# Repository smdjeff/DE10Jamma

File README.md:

# DE10Jamma

JAMMA/NeoGeo MVS audio, video & control IO for DE10-Nano.

[https://github.com/MisterJamma/DE10Jamma](https://github.com/MisterJamma/DE10Jamma)

Discussion thread: [https://www.atari-forum.com/viewtopic.php?f=120&t=38793](https://www.atari-forum.com/viewtopic.php?f=120&t=38793)

## Description

### Overview
DE10Jamma allows a DE10-Nano board to be connected directly to an arcade cabinet as simply as possible. USB and HDMI serial interfaces are not used, in order to remain as close as possible to the original arcade hardware and avoid unnecessary cost or complexity.

Pull-down resistors on AUDIO_L and AUDIO_R pins allow this board to be detected and coexist with other MiSTer hardware using common rbf files for the cores. See [this commit](https://github.com/MisterJamma/Arcade-GnG_MiSTer/commit/6c7786a7f790a5277f337f6b245e99f6ca4c25ff).

##### Future Developments
Future developments in RTL and software to more fully support DE10Jamma

1. Allow player controls to be used in the OSD.

### Inputs
Inputs are [RC filtered](https://wiki.neogeodev.org/index.php?title=CRE401) to give EMI protection to the FPGA.

No multiplexing, polling or debouncing of the inputs ensures **zero** additional latency & jitter. Cabinet switches are presented to arcade cores exactly as they would be on a real arcade PCB. Arcade cores will include necessary debouncing either in replicated hardware of the original PCB, or in software running on that hardware. When buttons are passed to the ARM host CPU for controlling the UI & selecting arcade cores, the inputs should debounced appropriately in hardware or software.

### Audio Output
2 pole RC filters convert PWM output from DE10-Nano to analog signal. Mono/Stereo jumper JP1 allows stereo signal for MVS wired cabinets, or mono signal for JAMMA wired cabinets. With no jumper fitted, there will be no audio output for the left channel.

2 channel power amplifier drives the speaker loads.

### Video Output
Composite sync is generated by DE10-Nano.

Three 6bit R-2R DACs convert the digital output from DE10-Nano to analog RGB. A single 2R value used in parallel to generate the R value with tighter tolerance. Part-to-part tolerance is typically significantly better than absolute part tolerance, so using a single 2R value for all resistors in the DAC should improve linearity.

No additional latency or incompatibility from HDMI logic and low quality HDMI converters. Resistive DACs are commonly used on arcade PCBs, and allow the original odd resolutions & refresh rates to be supported correctly. Output level is not noticeably lower than a NeoGeo MVS, and well within adjustment range on arcade monitors.

### DC Power Output
DC power output is provided for the DE10-Nano. This should be connected using a short [2.1mm male-male cable](https://www.google.com/search?q=2.1mm+male+to+male&tbm=isch), such as used to connect guitar effects pedals to a power supply.

Arcade power supplies are typically adjustable. DE10-Nano has regulation for lower voltage supplies, and should operate correctly from nominal +5v settings. If +5v rail is adjusted too high, the DE10-Nano's over-voltage protection circuitry will not allow the board to power up.

## Parts List
See BOM in fabrication outputs file

###### Notes
   1. Part numbers from [LSSC](https://lcsc.com/) are provided where possible. Values for some components do not match the schematic, and have been adjusted to reduce the number of different components.

   1. J1, J2 and J6 should be inserted into PCB from above, using DE10-Nano to set correct depth. Solder carefully from above & trim to length. Pins should protrude approximately 0.25" from the PCB

   1. J9 is only required for cabinets with 2.5mm pitch JST kick harness connector. It may also be possible to use 0.1" pitch J11 connector with existing kick harness, as the difference in pitch is minimal for a 10way connector.

   1. A 20mm deep fan running on a lower voltage is recommended for reduced noise.

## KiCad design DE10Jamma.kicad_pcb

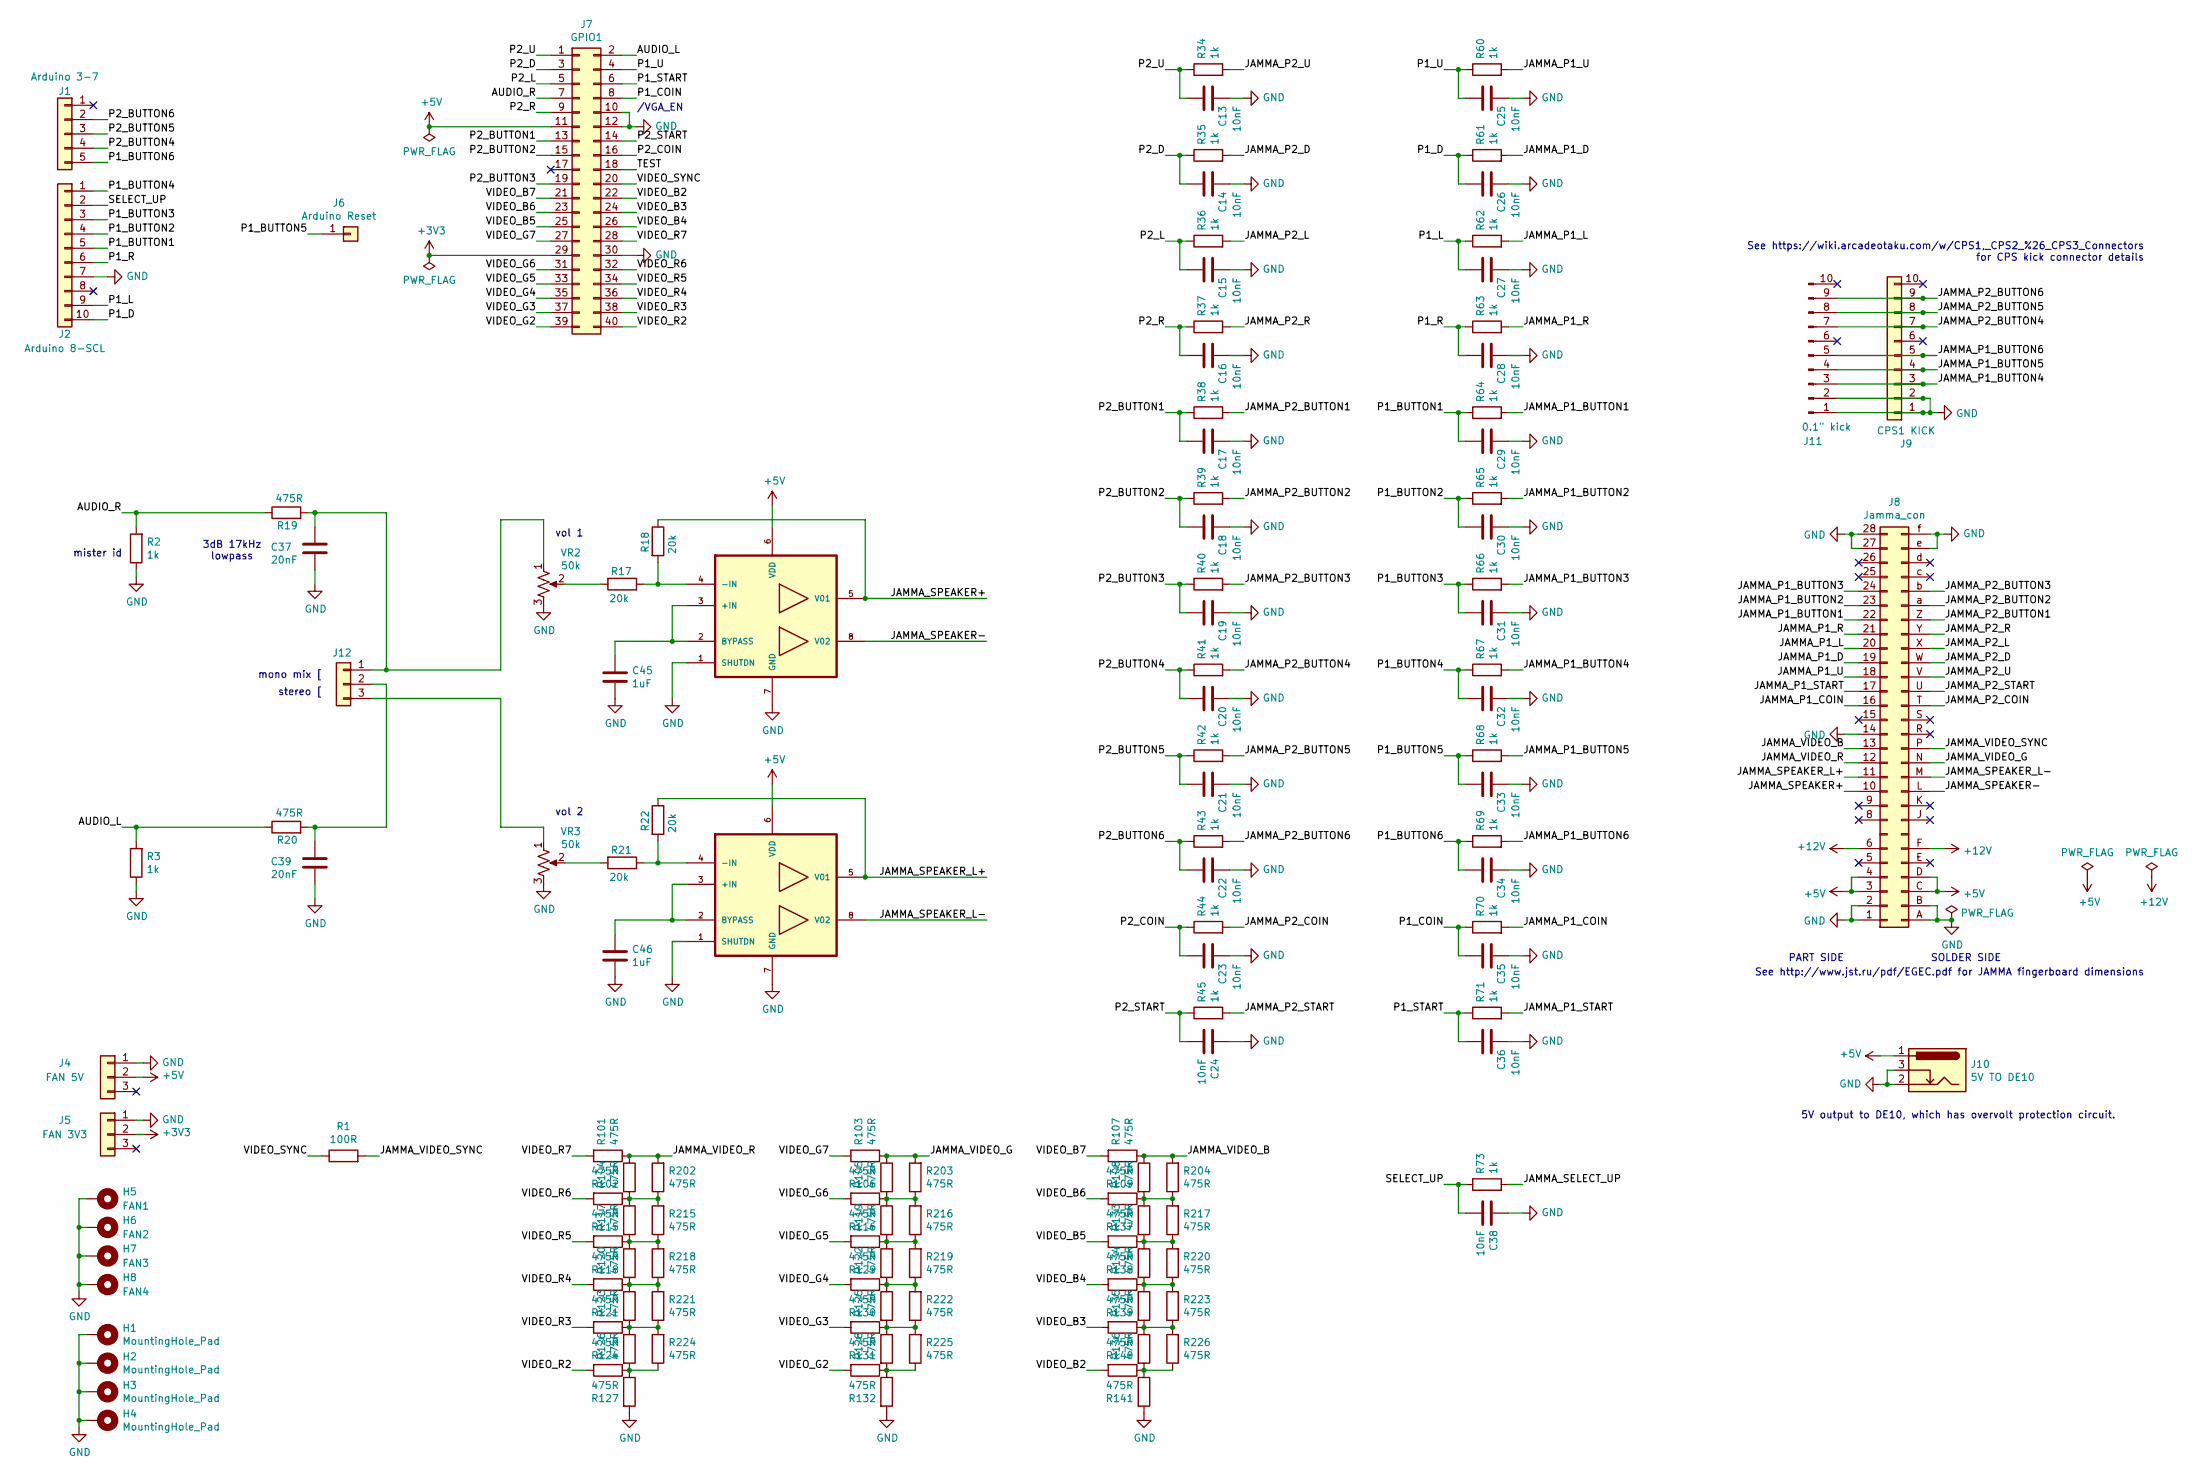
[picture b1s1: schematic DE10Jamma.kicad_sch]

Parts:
C13, C14, C15, C16, C17, C18, C19, C20, C21, C22, C23, C24, C25, C26, C27, C28, C29, C30, C31, C32, C33, C34, C35, C36, C38: 10nF; C_0402_1005Metric
C37, C39: 20nF; C_0402_1005Metric
C45, C46: 1uF; C_0603_1608Metric
H1, H2, H3, H4: MountingHole_Pad; MountingHole_3mm_Pad_Via
H5: FAN1; MountingHole_3mm
H6: FAN2; MountingHole_3mm
H7: FAN3; MountingHole_3mm
H8: FAN4; MountingHole_3mm
J1: Arduino 3-7; PinHeader_1x05_P2.54mm_Vertical
J2: Arduino 8-SCL; PinHeader_1x10_P2.54mm_Vertical
J4, J12: FAN 5V; PinHeader_1x03_P2.54mm_Vertical
J5: FAN 3V3; PinHeader_1x03_P2.54mm_Vertical
J6: Arduino Reset; PinHeader_1x01_P2.54mm_Vertical
J7: GPIO1; PinSocket_2x20_P2.54mm_Vertical
J8: Jamma_con; JAMMA-56
J9: CPS1 KICK; JST_EH_B10B-EH-A_1x10_P2.50mm_Vertical
J10: 5V TO DE10; BarrelJack_Horizontal
J11: 0.1" kick; PinHeader_1x10_P2.54mm_Vertical
R1: 100R; R_0402_1005Metric
R2, R3, R34, R35, R36, R37, R38, R39, R40, R41, R42, R43, R44, R45, R60, R61, R62, R63, R64, R65, R66, R67, R68, R69, R70, R71, R73: 1k; R_0402_1005Metric
R17, R18, R21, R22: 20k; R_0402_1005Metric
R19, R20, R101, R102, R103, R104, R105, R106, R107, R108, R109, R115, R116, R117, R118, R119, R120, R121, R122, R123, R124, R125, R126, R127, R128, R129, R130, R131, R132, R133, R134, R135, R136, R137, R138, R139, R140, R141, R202, R203, R204, R215, R216, R217, R218, R219, R220, R221, R222, R223, R224, R225, R226: 475R; R_0402_1005Metric
U3, U4: LM4871MX_NOPB; SOIC127P599X175-8N
VR2, VR3: 50k; PTV09A4020FB103; Manufacturer_Part_Number PTV09A-4020U-A503; Mouser Part Number 652-PTV09A-4020UA503

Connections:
+3V3: J5.2, J7.29
+5V: J4.2, J7.11, J8.3 (+5V), J8.4 (+5V), J8.C (+5V), J8.D (+5V), J10.1, U3.6 (VDD), U4.6 (VDD)
+12V: J8.6 (+12V), J8.F (+12V)
/AUDIO_L: J7.2, R3.2, R20.1
/AUDIO_R: J7.7, R2.2, R19.1
/JAMMA_P1_BUTTON1: J8.22 (P1_BUTTON_1), R64.2
/JAMMA_P1_BUTTON2: J8.23 (P1_BUTTON_2), R65.2
/JAMMA_P1_BUTTON3: J8.24 (P1_BUTTON_3), R66.2
/JAMMA_P1_BUTTON4: J9.3, J11.3, R67.2
/JAMMA_P1_BUTTON5: J9.4, J11.4, R68.2
/JAMMA_P1_BUTTON6: J9.5, J11.5, R69.2
/JAMMA_P1_COIN: J8.16 (COIN_1), R70.2
/JAMMA_P1_D: J8.19 (P1_DOWN), R61.2
/JAMMA_P1_L: J8.20 (P1_LEFT), R62.2
/JAMMA_P1_R: J8.21 (P1_RIGHT), R63.2
/JAMMA_P1_START: J8.17 (START_1), R71.2
/JAMMA_P1_U: J8.18 (P1_UP), R60.2
/JAMMA_P2_BUTTON1: J8.Z (P2_BUTTON_1), R38.2
/JAMMA_P2_BUTTON2: J8.a (P2_BUTTON_2), R39.2
/JAMMA_P2_BUTTON3: J8.b (P2_BUTTON_3), R40.2
/JAMMA_P2_BUTTON4: J9.7, J11.7, R41.2
/JAMMA_P2_BUTTON5: J9.8, J11.8, R42.2
/JAMMA_P2_BUTTON6: J9.9, J11.9, R43.2
/JAMMA_P2_COIN: J8.T (COIN_2), R44.2
/JAMMA_P2_D: J8.W (P2_DOWN), R35.2
/JAMMA_P2_L: J8.X (P2_LEFT), R36.2
/JAMMA_P2_R: J8.Y (P2_RIGHT), R37.2
/JAMMA_P2_START: J8.U (START_2), R45.2
/JAMMA_P2_U: J8.V (P2_UP), R34.2
/JAMMA_SELECT_UP: R73.2
/JAMMA_SPEAKER+: J8.10 (SPEAKER+), R18.1, U3.5 (V01)
/JAMMA_SPEAKER-: J8.L (SPEAKER-), U3.8 (V02)
/JAMMA_SPEAKER_L+: J8.11 (AUDIO+), R22.1, U4.5 (V01)
/JAMMA_SPEAKER_L-: J8.M (TEST), U4.8 (V02)
/JAMMA_VIDEO_B: J8.13 (VIDEO_BLUE), R107.1, R109.1, R204.2
/JAMMA_VIDEO_G: J8.N (VIDEO_GREEN), R103.1, R106.1, R203.2
/JAMMA_VIDEO_R: J8.12 (VIDEO_RED), R101.1, R102.1, R202.2
/JAMMA_VIDEO_SYNC: J8.P (VIDEO_SYNC), R1.2
/P1_BUTTON1: C29.2, J2.5, R64.1
/P1_BUTTON2: C30.2, J2.4, R65.1
/P1_BUTTON3: C31.2, J2.3, R66.1
/P1_BUTTON4: C32.2, J2.1, R67.1
/P1_BUTTON5: C33.2, J6.1, R68.1
/P1_BUTTON6: C34.2, J1.5, R69.1
/P1_COIN: C35.2, J7.8, R70.1
/P1_D: C26.2, J2.10, R61.1
/P1_L: C27.2, J2.9, R62.1
/P1_R: C28.2, J2.6, R63.1
/P1_START: C36.2, J7.6, R71.1
/P1_U: C25.2, J7.4, R60.1
/P2_BUTTON1: C17.2, J7.13, R38.1
/P2_BUTTON2: C18.2, J7.15, R39.1
/P2_BUTTON3: C19.2, J7.19, R40.1
/P2_BUTTON4: C20.2, J1.4, R41.1
/P2_BUTTON5: C21.2, J1.3, R42.1
/P2_BUTTON6: C22.2, J1.2, R43.1
/P2_COIN: C23.2, J7.16, R44.1
/P2_D: C14.2, J7.3, R35.1
/P2_L: C15.2, J7.5, R36.1
/P2_R: C16.2, J7.9, R37.1
/P2_START: C24.2, J7.14, R45.1
/P2_U: C13.2, J7.1, R34.1
/SELECT_UP: C38.2, J2.2, R73.1
/TEST: J7.18
/VIDEO_B2: J7.22, R136.2
/VIDEO_B3: J7.24, R135.2
/VIDEO_B4: J7.26, R134.2
/VIDEO_B5: J7.25, R133.2
/VIDEO_B6: J7.23, R108.2
/VIDEO_B7: J7.21, R107.2
/VIDEO_G2: J7.39, R128.2
/VIDEO_G3: J7.37, R125.2
/VIDEO_G4: J7.35, R122.2
/VIDEO_G5: J7.33, R119.2
/VIDEO_G6: J7.31, R105.2
/VIDEO_G7: J7.27, R103.2
/VIDEO_R2: J7.40, R126.2
/VIDEO_R3: J7.38, R123.2
/VIDEO_R4: J7.36, R120.2
/VIDEO_R5: J7.34, R117.2
/VIDEO_R6: J7.32, R104.2
/VIDEO_R7: J7.28, R101.2
/VIDEO_SYNC: J7.20, R1.1
GND: C13.1, C14.1, C15.1, C16.1, C17.1, C18.1, C19.1, C20.1, C21.1, C22.1, C23.1, C24.1, C25.1, C26.1, C27.1, C28.1, C29.1, C30.1, C31.1, C32.1, C33.1, C34.1, C35.1, C36.1, C37.1, C38.1, C39.1, C45.2, C46.2, H1.1, H2.1, H3.1, H4.1, H5.1, H6.1, H7.1, H8.1, J2.7, J4.1, J5.1, J7.10, J7.12, J7.30, J8.1 (GND), J8.2 (GND), J8.14 (VIDEO_GND), J8.27 (GND), J8.28 (GND), J8.A (GND), J8.B (GND), J8.e (GND), J8.f (GND), J9.1, J9.2, J10.2, J10.3, J11.1, J11.2, R2.1, R3.1, R127.2, R132.2, R141.2, U3.1 (SHUTDN), U3.7 (GND), U4.1 (SHUTDN), U4.7 (GND), VR2.3, VR3.3
unnamed: C37.2, J12.1, R19.2, VR2.1
unnamed: C39.2, J12.2, R20.2
unnamed: J12.3, VR3.1
unnamed: R17.2, VR2.2
unnamed: R21.2, VR3.2
unnamed: R102.2, R104.1, R115.1, R202.1, R215.2
unnamed: R105.1, R106.2, R116.1, R203.1, R216.2
unnamed: R108.1, R109.2, R137.1, R204.1, R217.2
unnamed: R115.2, R117.1, R118.1, R215.1, R218.2
unnamed: R116.2, R119.1, R129.1, R216.1, R219.2
unnamed: R118.2, R120.1, R121.1, R218.1, R221.2
unnamed: R121.2, R123.1, R124.1, R221.1, R224.2
unnamed: R122.1, R129.2, R130.1, R219.1, R222.2
unnamed: R124.2, R126.1, R127.1, R224.1
unnamed: R125.1, R130.2, R131.1, R222.1, R225.2
unnamed: R128.1, R131.2, R132.1, R225.1
unnamed: R133.1, R137.2, R138.1, R217.1, R220.2
unnamed: R134.1, R138.2, R139.1, R220.1, R223.2
unnamed: R135.1, R139.2, R140.1, R223.1, R226.2
unnamed: R136.1, R140.2, R141.1, R226.1
unnamed: C45.1, U3.2 (BYPASS), U3.3 (+IN)
unnamed: R17.1, R18.2, U3.4 (-IN)
unnamed: C46.1, U4.2 (BYPASS), U4.3 (+IN)
unnamed: R21.1, R22.2, U4.4 (-IN)

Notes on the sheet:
5V output to DE10, which has overvolt protection circuit.
vol 2
stereo [
vol 1
mister id
3dB 17kHz lowpass
/VGA_EN
See http://www.jst.ru/pdf/EGEC.pdf for JAMMA fingerboard dimensions
mono mix [
SOLDER SIDE
PART SIDE
See https://wiki.arcadeotaku.com/w/CPS1,_CPS2_%26_CPS3_Connectors for CPS kick connector details

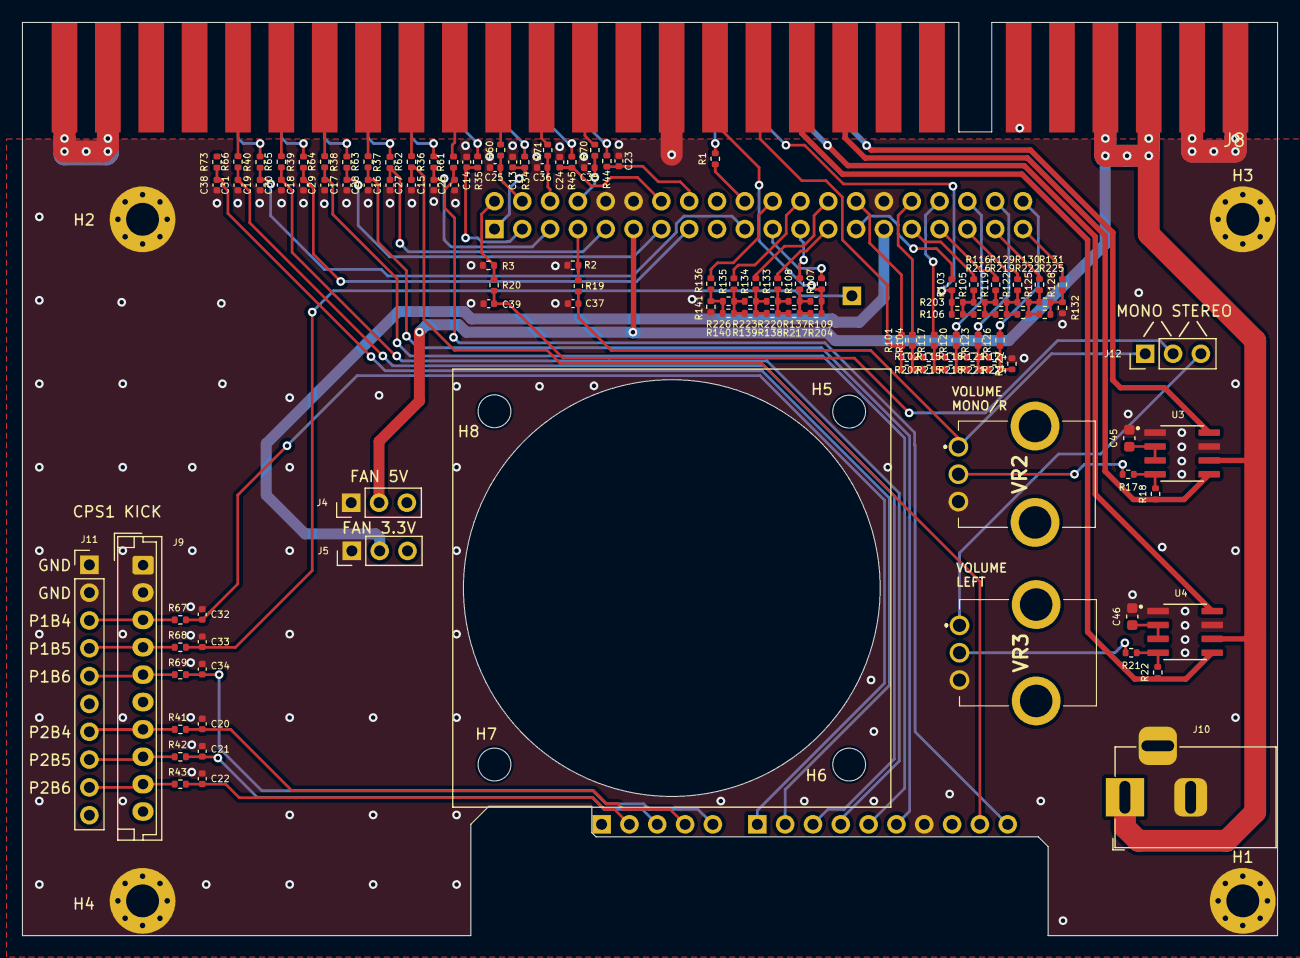
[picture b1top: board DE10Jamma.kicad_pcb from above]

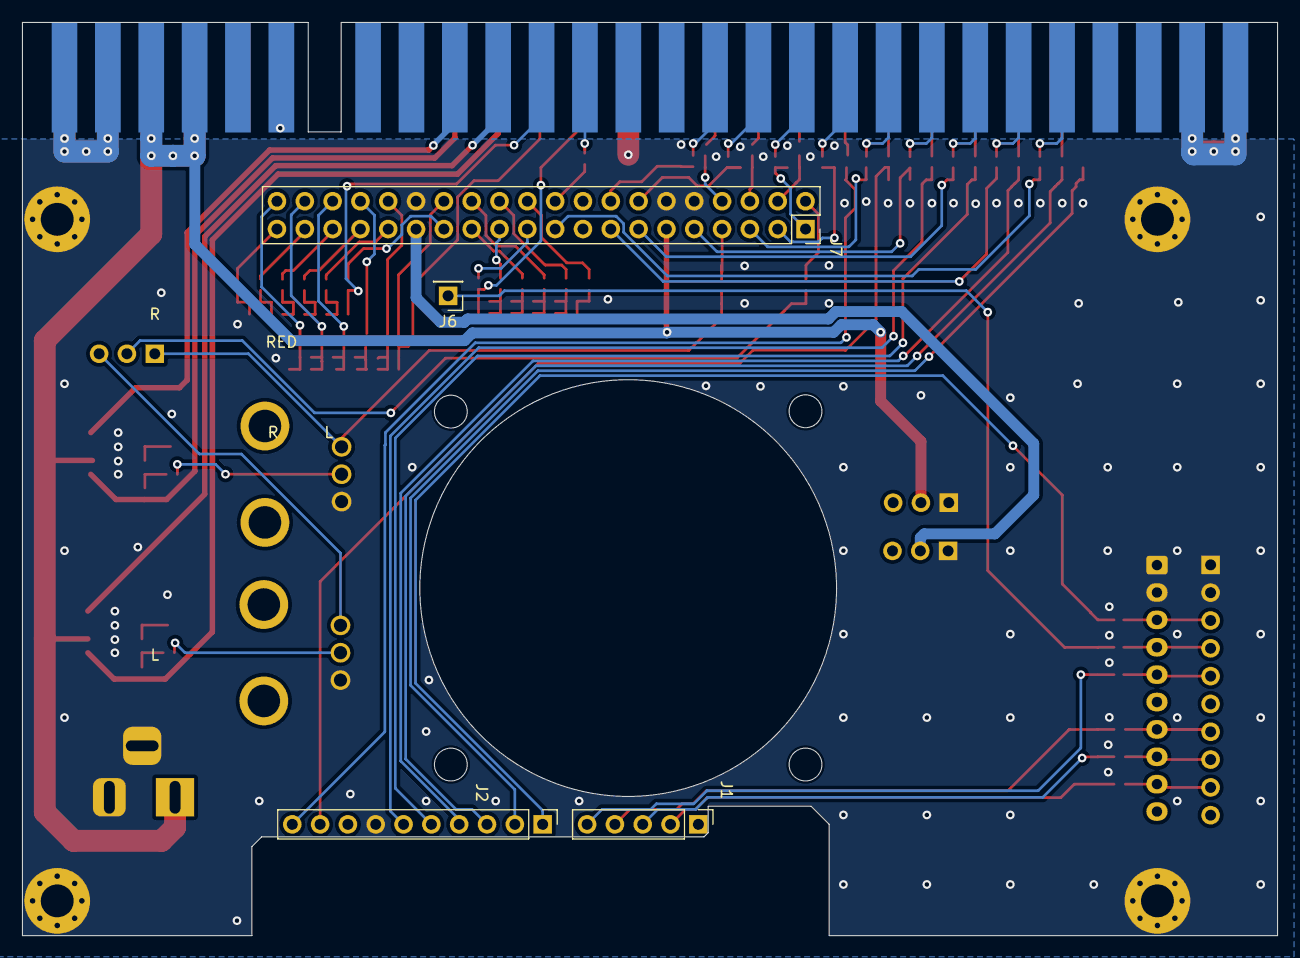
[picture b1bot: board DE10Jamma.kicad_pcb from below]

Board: 2 copper layers, 114.6 x 83.4 mm, 137 parts (4 on the bottom side), 106 nets.

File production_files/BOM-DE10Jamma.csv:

Comment,Designator,Footprint,LCSC,Quantity
1k,"R2,R3,R34,R35,R36,R37,R38,R39,R40,R41,R42,R43,R44,R45,R60,R61,R62,R63,R64,R65,R66,R67,R68,R69,R70,R71,R73",R_0402_1005Metric,C11702,27
10nF,"C13,C14,C15,C16,C17,C18,C19,C20,C21,C22,C23,C24,C25,C26,C27,C28,C29,C30,C31,C32,C33,C34,C35,C36,C38",C_0402_1005Metric,C15195,25
1uF,"C45,C46",C_0603_1608Metric,C15849,2
CPS1 KICK,J9,JST_EH_B10B-EH-A_1x10_P2.50mm_Vertical,C160365,1
100R,R1,R_0402_1005Metric,C25076,1
20k,"R17,R18,R21,R22",R_0402_1005Metric,C25765,4
5V TO DE10,J10,BarrelJack_Horizontal,C319099,1
20nF,"C37,C39",C_0402_1005Metric,C5448807,2
LM4871MX_NOPB,"U3,U4",SOIC127P599X175-8N,C7554,2
475R,"R101,R102,R103,R104,R105,R106,R107,R108,R109,R115,R116,R117,R118,R119,R120,R121,R122,R123,R124,R125,R126,R127,R128,R129,R130,R131,R132,R133,R134,R135,R136,R137,R138,R139,R140,R141,R19,R20,R202,R203,R204,R215,R216,R217,R218,R219,R220,R221,R222,R223,R224,R225,R226",R_0402_1005Metric,C852800,53

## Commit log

2025-06-24 add some interesting part libraries.
2025-06-24 single side assembly, swap out amplifier to a more common part, use common 0402 discrete resistors.
2025-06-24 reorg files
2025-06-24 converted from Eagle to KiCad

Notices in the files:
DE10Jamma.kicad_pcb:
V2.0 (C)2025
